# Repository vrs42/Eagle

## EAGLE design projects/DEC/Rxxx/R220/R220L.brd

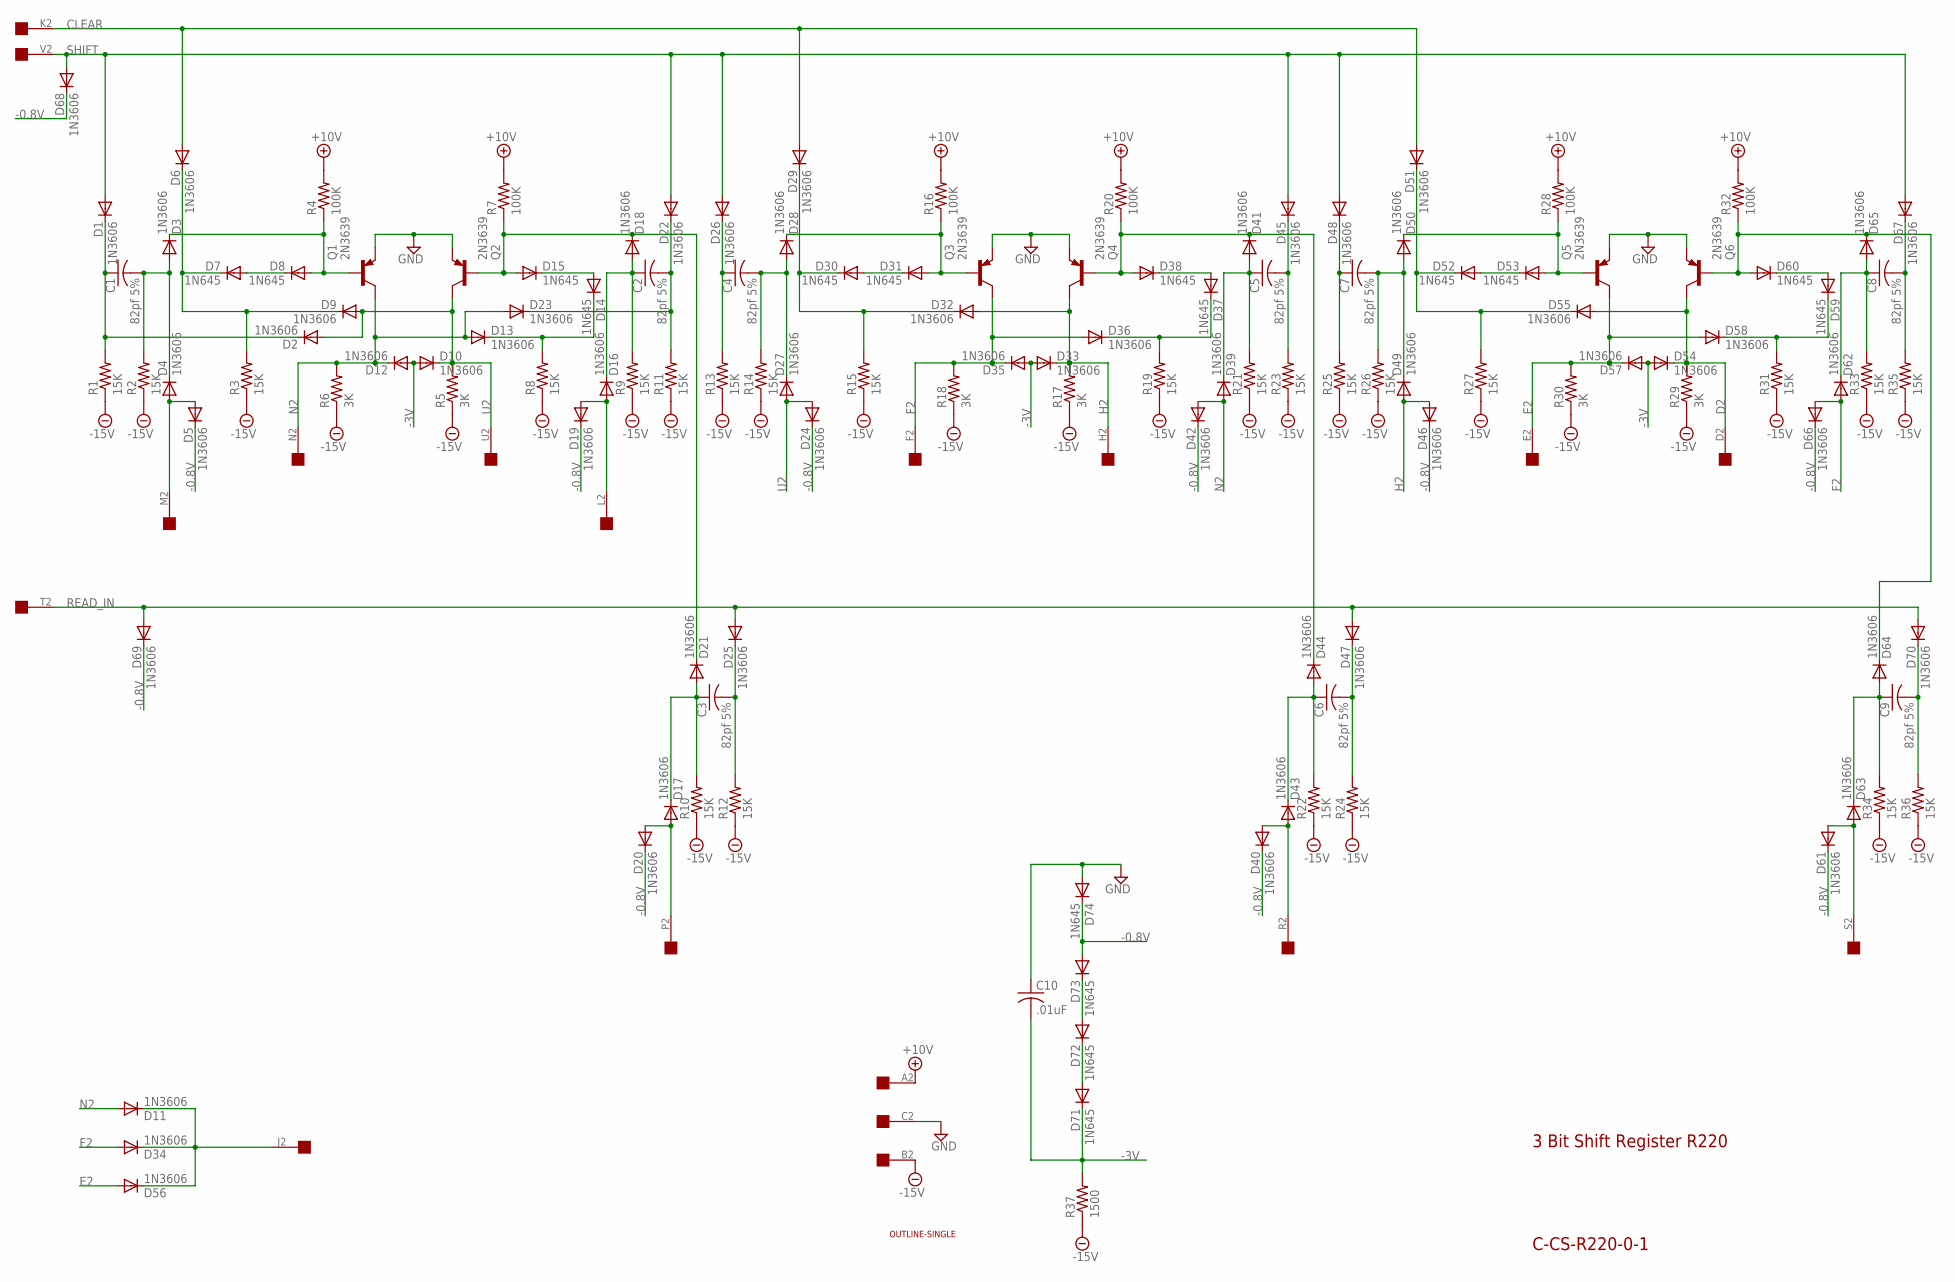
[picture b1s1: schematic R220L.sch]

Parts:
C1, C2, C3, C4, C5, C6, C7, C8, C9: 82pf 5%; C063-025X075
C10: .01uF; C063-025X075
D1, D2, D3, D4, D5, D6, D9, D10, D11, D12, D13, D16, D17, D18, D19, D20, D21, D22, D23, D24, D25, D26, D27, D28, D29, D32, D33, D34, D35, D36, D39, D40, D41, D42, D43, D44, D45, D46, D47, D48, D49, D50, D51, D54, D55, D56, D57, D58, D61, D62, D63, D64, D65, D66, D67, D68, D69, D70: 1N3606; DO35-10
D7, D8, D14, D15, D30, D31, D37, D38, D52, D53, D59, D60, D71, D72, D73, D74: 1N645; DO35-10
Q1, Q2, Q3, Q4, Q5, Q6: 2N3639; TO39
R1, R2, R3, R8, R9, R10, R11, R12, R13, R14, R15, R19, R21, R22, R23, R24, R25, R26, R27, R31, R33, R34, R35, R36: 15K; 0207/10
R4, R7, R16, R20, R28, R32: 100K; 0207/10
R5, R6, R17, R18, R29, R30: 3K; 0207/10
R37: 1500; 0207/10
U$1: OUTLINE-SINGLE; SINGLE
U$2: EDGE-1; EDGE-CON1

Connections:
+10V: R4.2, R7.2, R16.2, R20.2, R28.2, R32.2, U$2.A2
-0.8V: D5.C, D19.C, D20.C, D24.C, D40.C, D42.C, D46.C, D61.C, D66.C, D68.C, D69.C, D73.A, D74.C
-3V: C10.2, D10.A, D12.A, D33.A, D35.A, D54.A, D57.A, D71.C, R37.2
-15V: R1.1, R2.1, R3.1, R5.1, R6.1, R8.1, R9.1, R10.1, R11.1, R12.1, R13.1, R14.1, R15.1, R17.1, R18.1, R19.1, R21.1, R22.1, R23.1, R24.1, R25.1, R26.1, R27.1, R29.1, R30.1, R31.1, R33.1, R34.1, R35.1, R36.1, R37.1, U$2.B2
CLEAR: D6.A, D29.A, D51.A, U$2.K2
D2: D54.C, D55.A, Q6.3 (C), R29.2, U$2.D2
E2: D56.A, D57.C, D58.A, Q5.3 (C), R30.2, U$2.E2
F2: D34.A, D35.C, D36.A, D62.A, D66.A, Q3.3 (C), R18.2, U$2.F2
GND: C10.1, D74.A, Q1.1 (E), Q2.1 (E), Q3.1 (E), Q4.1 (E), Q5.1 (E), Q6.1 (E), U$2.C2
H2: D32.A, D33.C, D46.A, D49.A, Q4.3 (C), R17.2, U$2.H2
N2: D11.A, D12.C, D13.A, D23.A, D39.A, D42.A, Q1.3 (C), R6.2, U$2.N2
unnamed: D30.A, D31.C
unnamed: C2.2, D22.C, D23.C, R11.2
unnamed: D29.C, D30.C, D32.C, R15.2
unnamed: C1.1, D1.C, D2.C, R1.2
unnamed: D14.A, D15.C
unnamed: C1.2, D3.A, D4.C, R2.2
unnamed: C2.1, D16.C, D18.A, R9.2
unnamed: D6.C, D7.C, D9.C, R3.2
unnamed: D4.A, D5.A, U$2.M2
unnamed: D28.C, D31.A, Q3.2 (B), R16.1
unnamed: D13.C, D14.C, R8.2
unnamed: D37.A, D38.C
unnamed: D3.C, D8.A, Q1.2 (B), R4.1
unnamed: D38.A, D41.C, D44.C, Q4.2 (B), R20.1
unnamed: D36.C, D37.C, R19.2
unnamed: D15.A, D18.C, D21.C, Q2.2 (B), R7.1
unnamed: C4.1, D26.C, R13.2
unnamed: C4.2, D27.C, D28.A, R14.2
unnamed: C5.1, D39.C, D41.A, R21.2
unnamed: D7.A, D8.C
unnamed: D11.C, D34.C, D56.C, U$2.J2
unnamed: C5.2, D45.C, R23.2
unnamed: D52.A, D53.C
unnamed: D51.C, D52.C, D55.C, R27.2
unnamed: D50.C, D53.A, Q5.2 (B), R28.1
unnamed: D59.A, D60.C
unnamed: D60.A, D64.C, D65.C, Q6.2 (B), R32.1
unnamed: D16.A, D19.A, U$2.L2
unnamed: D58.C, D59.C, R31.2
unnamed: C7.1, D48.C, R25.2
unnamed: C7.2, D49.C, D50.A, R26.2
unnamed: D71.A, D72.C
unnamed: C8.1, D62.C, D65.A, R33.2
unnamed: C8.2, D67.C, R35.2
unnamed: D72.A, D73.C
unnamed: C3.1, D17.C, D21.A, R10.2
unnamed: C3.2, D25.C, R12.2
unnamed: C6.1, D43.C, D44.A, R22.2
unnamed: C6.2, D47.C, R24.2
unnamed: C9.1, D63.C, D64.A, R34.2
unnamed: C9.2, D70.C, R36.2
P2: D17.A, D20.A, U$2.P2
R2: D40.A, D43.A, U$2.R2
READ_IN: D25.A, D47.A, D69.A, D70.A, U$2.T2
S2: D61.A, D63.A, U$2.S2
SHIFT: D1.A, D22.A, D26.A, D45.A, D48.A, D67.A, D68.A, U$2.V2
U2: D2.A, D9.A, D10.C, D24.A, D27.A, Q2.3 (C), R5.2, U$2.U2

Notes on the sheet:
3 Bit Shift Register R220
C-CS-R220-0-1

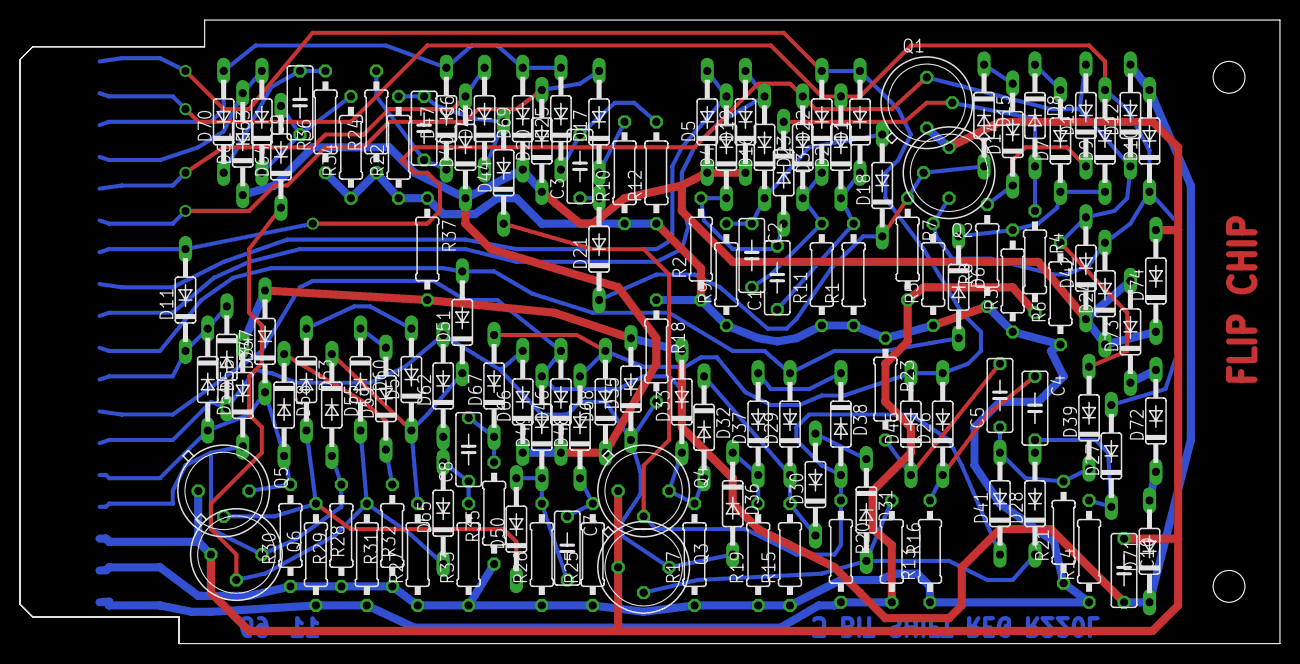
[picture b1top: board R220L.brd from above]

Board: 2 copper layers, 125.7 x 62.2 mm, 130 parts (0 on the bottom side), 58 nets.

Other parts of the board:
U$3: FLIPCHIP

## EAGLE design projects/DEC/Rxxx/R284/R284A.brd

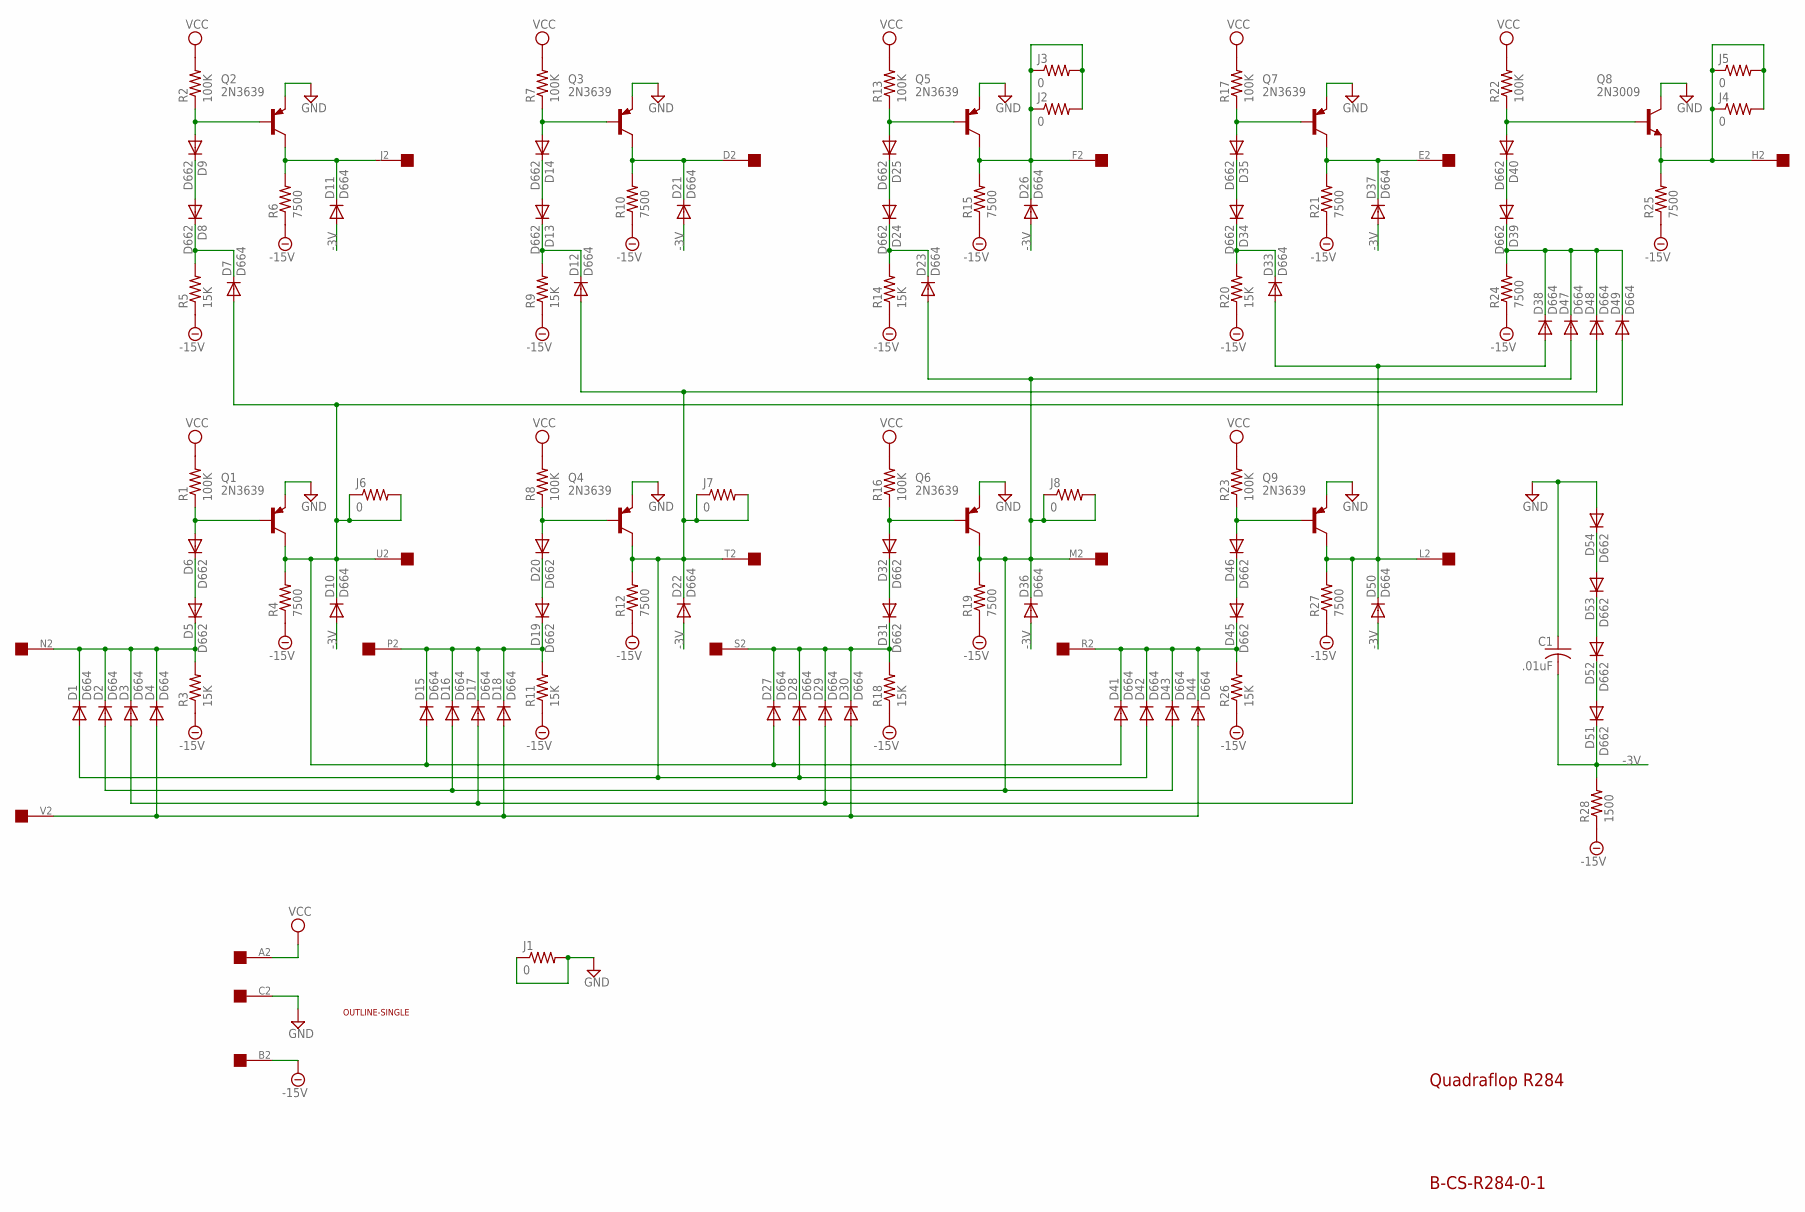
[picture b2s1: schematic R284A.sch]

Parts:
C1: .01uF; C063-025X075
D1, D2, D3, D4, D7, D10, D11, D12, D15, D16, D17, D18, D21, D22, D23, D26, D27, D28, D29, D30, D33, D36, D37, D38, D41, D42, D43, D44, D47, D48, D49, D50: D664; DO35-10
D5, D6, D8, D9, D13, D14, D19, D20, D24, D25, D31, D32, D34, D35, D39, D40, D45, D46, D51, D52, D53, D54: D662; DO35-10
J1, J2, J3, J4, J5, J6, J7, J8: 0; 0207/10
Q1, Q2, Q3, Q4, Q5, Q6, Q7, Q9: 2N3639; TO5
Q8: 2N3009; TO5
R1, R2, R7, R8, R13, R16, R17, R22, R23: 100K; 0207/10
R3, R5, R9, R11, R14, R18, R20, R26: 15K; 0207/10
R4, R6, R10, R12, R15, R19, R21, R24, R25, R27: 7500; 0207/10
R28: 1500; 0207/10
U$1: OUTLINE-SINGLE; SINGLE
U$2: EDGE-1; EDGE-CON1

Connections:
-3V: C1.2, D10.A, D11.A, D21.A, D22.A, D26.A, D36.A, D37.A, D50.A, D51.C, R28.2
-15V: R3.1, R4.1, R5.1, R6.1, R9.1, R10.1, R11.1, R12.1, R14.1, R15.1, R18.1, R19.1, R20.1, R21.1, R24.1, R25.1, R26.1, R27.1, R28.1, U$2.B2
GND: C1.1, D54.A, J1.1, J1.2, Q1.1 (E), Q2.1 (E), Q3.1 (E), Q4.1 (E), Q5.1 (E), Q6.1 (E), Q7.1 (E), Q8.3 (C), Q9.1 (E), U$2.C2
unnamed: D9.A, Q2.2 (B), R2.1
unnamed: D11.C, Q2.3 (C), R6.2, U$2.J2
unnamed: D7.C, D8.C, R5.2
unnamed: D8.A, D9.C
unnamed: D6.A, Q1.2 (B), R1.1
unnamed: D1.C, D2.C, D3.C, D4.C, D5.C, R3.2, U$2.N2
unnamed: D5.A, D6.C
unnamed: D7.A, D10.C, D15.A, D27.A, D41.A, D49.A, J6.1, J6.2, Q1.3 (C), R4.2, U$2.U2
unnamed: D1.A, D12.A, D22.C, D28.A, D42.A, D48.A, J7.1, J7.2, Q4.3 (C), R12.2, U$2.T2
unnamed: D2.A, D16.A, D23.A, D36.C, D43.A, D47.A, J8.1, J8.2, Q6.3 (C), R19.2, U$2.M2
unnamed: D3.A, D17.A, D29.A, D33.A, D38.A, D50.C, Q9.3 (C), R27.2, U$2.L2
unnamed: D4.A, D18.A, D30.A, D44.A, U$2.V2
unnamed: D14.A, Q3.2 (B), R7.1
unnamed: D21.C, Q3.3 (C), R10.2, U$2.D2
unnamed: D12.C, D13.C, R9.2
unnamed: D13.A, D14.C
unnamed: D20.A, Q4.2 (B), R8.1
unnamed: D15.C, D16.C, D17.C, D18.C, D19.C, R11.2, U$2.P2
unnamed: D19.A, D20.C
unnamed: D51.A, D52.C
unnamed: D52.A, D53.C
unnamed: D53.A, D54.C
unnamed: D25.A, Q5.2 (B), R13.1
unnamed: D26.C, J2.1, J2.2, J3.1, J3.2, Q5.3 (C), R15.2, U$2.F2
unnamed: D23.C, D24.C, R14.2
unnamed: D24.A, D25.C
unnamed: D32.A, Q6.2 (B), R16.1
unnamed: D27.C, D28.C, D29.C, D30.C, D31.C, R18.2, U$2.S2
unnamed: D31.A, D32.C
unnamed: D35.A, Q7.2 (B), R17.1
unnamed: D37.C, Q7.3 (C), R21.2, U$2.E2
unnamed: D33.C, D34.C, R20.2
unnamed: D34.A, D35.C
unnamed: D46.A, Q9.2 (B), R23.1
unnamed: D41.C, D42.C, D43.C, D44.C, D45.C, R26.2, U$2.R2
unnamed: D45.A, D46.C
unnamed: D40.A, Q8.2 (B), R22.1
unnamed: J4.1, J4.2, J5.1, J5.2, Q8.1 (E), R25.2, U$2.H2
unnamed: D38.C, D39.C, D47.C, D48.C, D49.C, R24.2
unnamed: D39.A, D40.C
VCC: R1.2, R2.2, R7.2, R8.2, R13.2, R16.2, R17.2, R22.2, R23.2, U$2.A2

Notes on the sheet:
B-CS-R284-0-1
Quadraflop R284

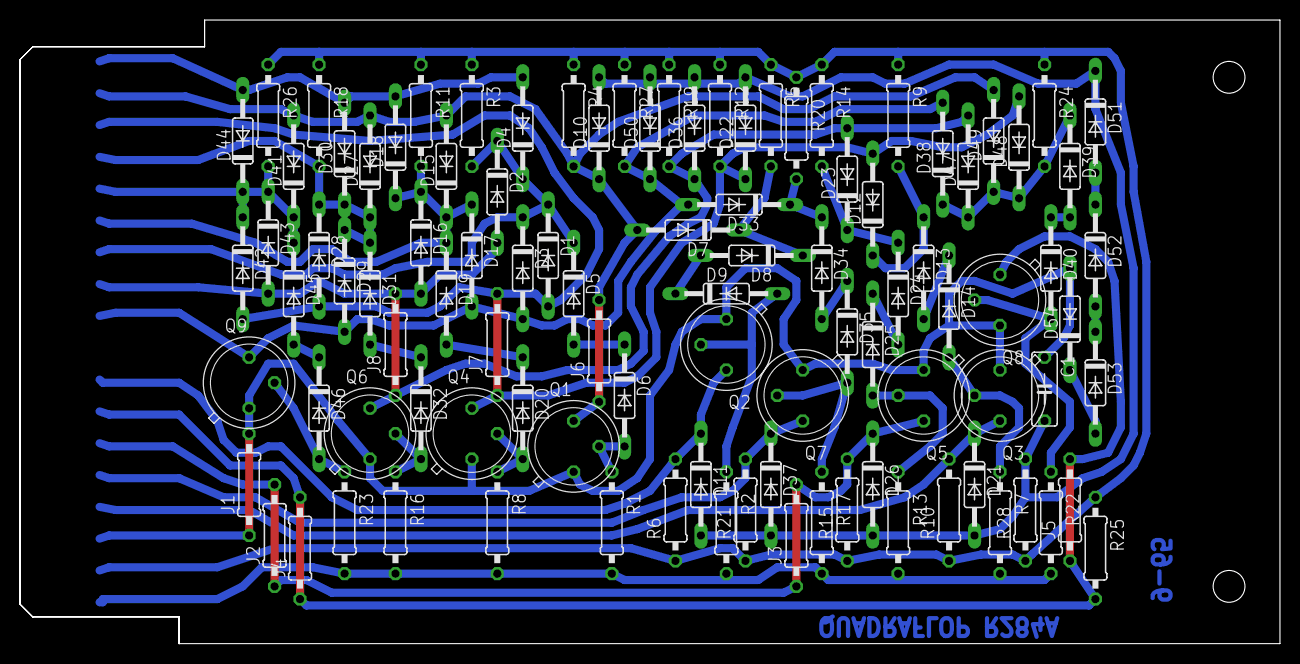
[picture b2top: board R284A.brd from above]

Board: 2 copper layers, 125.7 x 62.2 mm, 102 parts (0 on the bottom side), 44 nets.

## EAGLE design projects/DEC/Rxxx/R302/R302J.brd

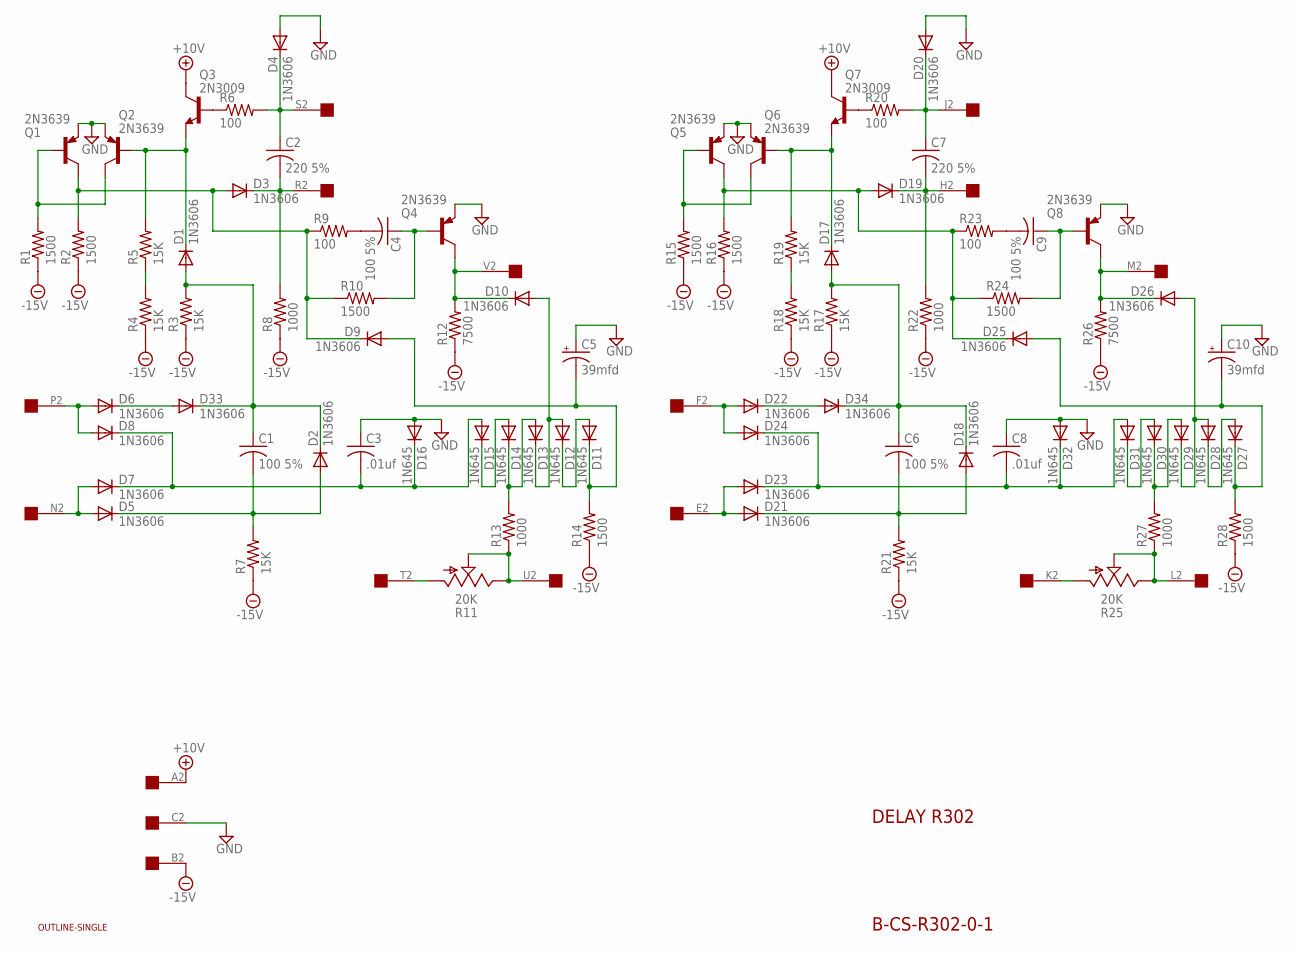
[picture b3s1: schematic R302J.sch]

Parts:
C1, C4, C6, C9: 100 5%; C050-025X075
C2, C7: 220 5%; C050-025X075
C3, C8: .01uf; C050-025X075
C5, C10: 39mfd; E15-5
D1, D2, D3, D4, D5, D6, D7, D8, D9, D10, D17, D18, D19, D20, D21, D22, D23, D24, D25, D26, D33, D34: 1N3606; DO35-10
D11, D12, D13, D14, D15, D16, D27, D28, D29, D30, D31, D32: 1N645; DO35-10
Q1, Q2, Q4, Q5, Q6, Q8: 2N3639; TO39
Q3, Q7: 2N3009; TO39
R1, R2, R10, R14, R15, R16, R24, R28: 1500; 0207/10
R3, R4, R5, R7, R17, R18, R19, R21: 15K; 0207/10
R6, R9, R20, R23: 100; 0207/10
R8, R13, R22, R27: 1000; 0207/10
R11, R25: 20K; SP19L
R12, R26: 7500; 0207/10
U$1: OUTLINE-SINGLE; SINGLE
U$2: EDGE-1; EDGE-CON1

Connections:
+10V: Q3.3 (C), Q7.3 (C), U$2.A2
-15V: R1.1, R2.1, R3.1, R4.1, R7.1, R8.1, R12.1, R14.1, R15.1, R16.1, R17.1, R18.1, R21.1, R22.1, R26.1, R28.1, U$2.B2
GND: C3.1, C5.+, C8.1, C10.+, D4.A, D16.A, D20.A, D32.A, Q1.1 (E), Q2.1 (E), Q4.1 (E), Q5.1 (E), Q6.1 (E), Q8.1 (E), U$2.C2
unnamed: C2.1, D4.C, R6.2, U$2.S2
unnamed: C2.2, D3.C, R8.2, U$2.R2
unnamed: D1.C, Q2.2 (B), Q3.1 (E), R5.2
unnamed: R4.2, R5.1
unnamed: D22.A, D24.A, U$2.F2
unnamed: Q3.2 (B), R6.1
unnamed: R11.E, R11.S, R13.1, U$2.U2
unnamed: C1.1, D1.A, D2.C, D33.C, R3.2
unnamed: D5.A, D7.A, U$2.N2
unnamed: R11.A, U$2.T2
unnamed: D6.C, D33.A
unnamed: D6.A, D8.A, U$2.P2
unnamed: C1.2, D2.A, D5.C, R7.2
unnamed: C3.2, D7.C, D8.C, D15.A, D16.C
unnamed: C4.2, R9.2
unnamed: Q1.2 (B), Q2.3 (C), R1.2
unnamed: C4.1, Q4.2 (B), R10.2
unnamed: D3.A, D9.C, Q1.3 (C), R2.2, R9.1, R10.1
unnamed: D10.C, Q4.3 (C), R12.2, U$2.V2
unnamed: Q5.2 (B), Q6.3 (C), R15.2
unnamed: D13.A, D14.C, R13.2
unnamed: D11.A, D12.C
unnamed: D19.A, D25.C, Q5.3 (C), R16.2, R23.1, R24.1
unnamed: C5.-, D9.A, D11.C, R14.2
unnamed: D17.C, Q6.2 (B), Q7.1 (E), R19.2
unnamed: Q7.2 (B), R20.1
unnamed: C7.1, D20.C, R20.2, U$2.J2
unnamed: C7.2, D19.C, R22.2, U$2.H2
unnamed: R18.2, R19.1
unnamed: D22.C, D34.A
unnamed: C6.1, D17.A, D18.C, D34.C, R17.2
unnamed: C6.2, D18.A, D21.C, R21.2
unnamed: D21.A, D23.A, U$2.E2
unnamed: C8.2, D23.C, D24.C, D31.A, D32.C
unnamed: C9.2, R23.2
unnamed: C9.1, Q8.2 (B), R24.2
unnamed: D26.C, Q8.3 (C), R26.2, U$2.M2
unnamed: D29.A, D30.C, R27.2
unnamed: D27.A, D28.C
unnamed: C10.-, D25.A, D27.C, R28.2
unnamed: R25.E, R25.S, R27.1, U$2.L2
unnamed: R25.A, U$2.K2
unnamed: D10.A, D12.A, D13.C
unnamed: D14.A, D15.C
unnamed: D30.A, D31.C
unnamed: D26.A, D28.A, D29.C

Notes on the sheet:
DELAY R302
B-CS-R302-0-1

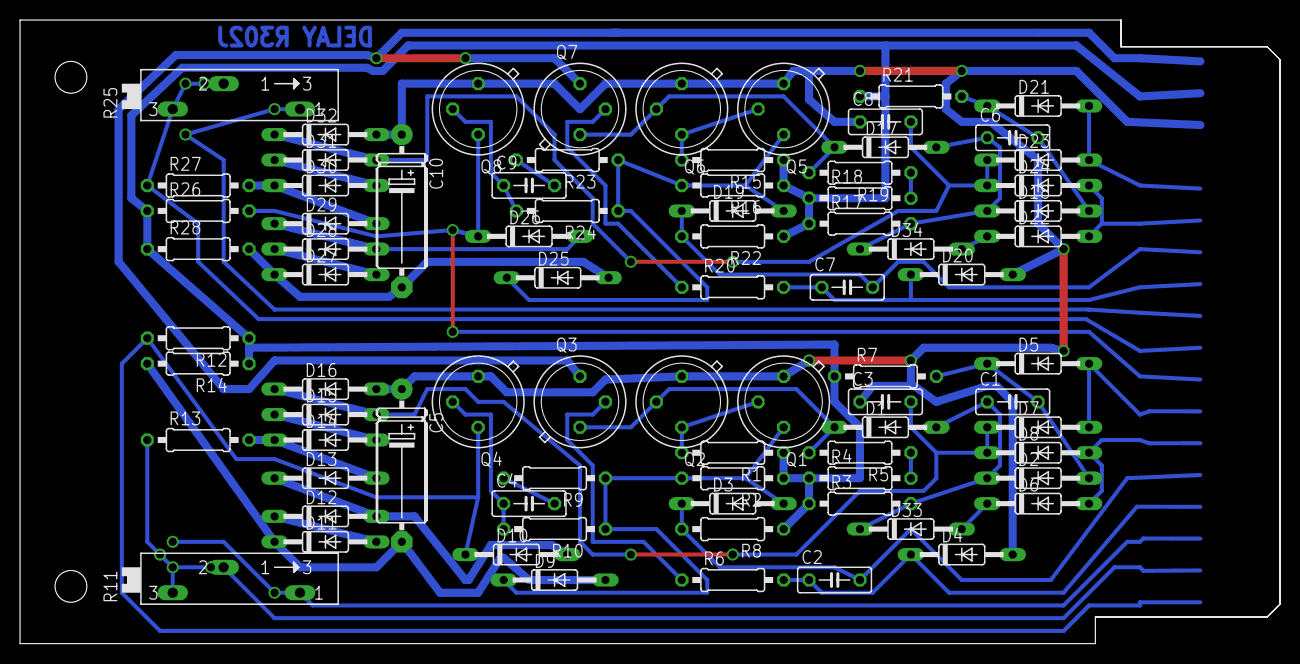
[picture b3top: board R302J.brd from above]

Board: 2 copper layers, 125.7 x 62.2 mm, 82 parts (0 on the bottom side), 49 nets.
